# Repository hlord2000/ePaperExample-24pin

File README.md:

# A KiCAD 8 Schematic for Waveshare/Good Display 24-pin ePaper Displays

Based on the Waveshare ePaper shield. Includes links to parametric search for critical components.  

**Please refer to the datasheet for your specific driver IC to confirm component values and specifications.**

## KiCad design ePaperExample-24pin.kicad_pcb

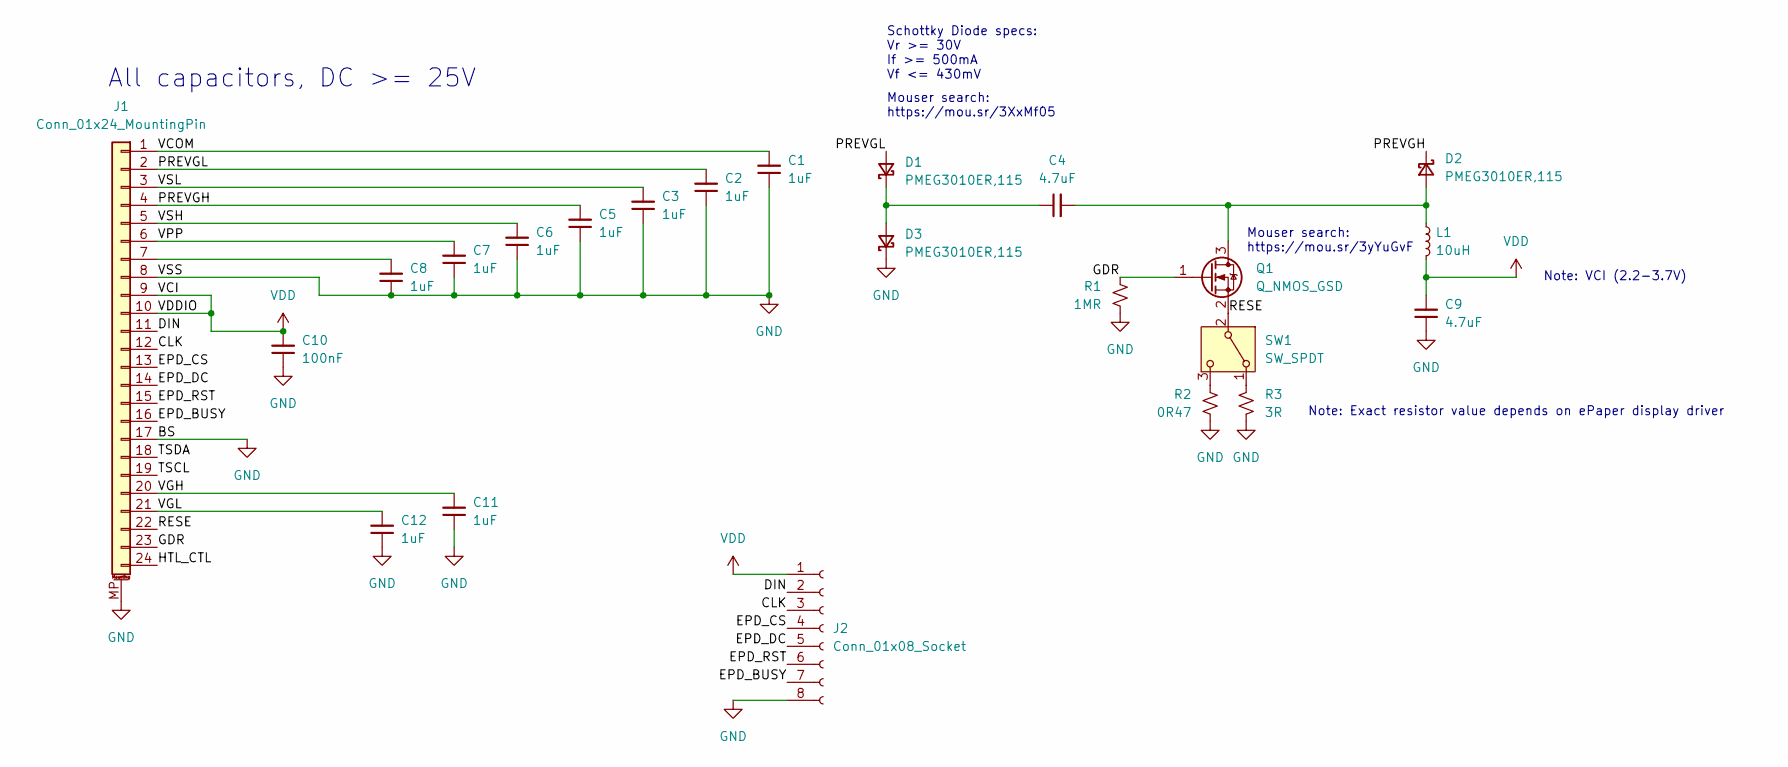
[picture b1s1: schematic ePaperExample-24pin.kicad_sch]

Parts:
C1, C2, C3, C5, C6, C7, C8, C11, C12: 1uF; C_0402_1005Metric; LCSC C52923
C4, C9: 4.7uF; C_0402_1005Metric; LCSC C2858031
C10: 100nF; C_0402_1005Metric; LCSC C307331
D1, D2, D3: PMEG3010ER,115; D_SOD-123; LCSC C456106
J1: Conn_01x24_MountingPin; TE_2-1734839-4_1x24-1MP_P0.5mm_Horizontal; LCSC C2911766
J2: Conn_01x08_Socket; PinHeader_1x08_P2.54mm_Vertical
L1: 10uH; L_0805_2012Metric; LCSC C2909263
Q1: Q_NMOS_GSD; SOT-23; LCSC C414015
R1: 1MR; R_0402_1005Metric; LCSC C26083
R2: 0R47; R_0603_1608Metric; LCSC C186564
R3: 3R; R_0603_1608Metric; LCSC C23157
SW1: SW_SPDT; SW_SPDT_PCM12; LCSC C109335

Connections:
/CLK: J1.12, J2.3
/DIN: J1.11, J2.2
/EPD_BUSY: J1.16, J2.7
/EPD_CS: J1.13, J2.4
/EPD_DC: J1.14, J2.5
/EPD_RST: J1.15, J2.6
/GDR: J1.23, Q1.1 (G), R1.1
/HTL_CTL: J1.24
/PREVGH: C5.2, D2.1 (K), J1.4
/PREVGL: C2.2, D1.2 (A), J1.2
/RESE: J1.22, Q1.2 (S), SW1.2 (B)
/TSCL: J1.19
/TSDA: J1.18
/VCOM: C1.2, J1.1
/VGH: C11.2, J1.20
/VGL: C12.2, J1.21
/VPP: C7.2, J1.6
/VSH: C6.2, J1.5
/VSL: C3.2, J1.3
GND: C1.1, C2.1, C3.1, C5.1, C6.1, C7.1, C8.1, C9.1, C10.1, C11.1, C12.1, D3.1 (K), J1.8, J1.17, J1.MP (MountPin), J2.8, R1.2, R2.2, R3.2
unnamed: C4.1, D1.1 (K), D3.2 (A)
unnamed: C4.2, D2.2 (A), L1.1, Q1.3 (D)
unnamed: C8.2, J1.7
unnamed: R3.1, SW1.1 (A)
unnamed: R2.1, SW1.3 (C)
VDD: C9.2, C10.2, J1.9, J1.10, J2.1, L1.2

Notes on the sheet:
Note: Exact resistor value depends on ePaper display driver
Note: VCI (2.2-3.7V)
Mouser search: https://mou.sr/3XxMf05
All capacitors, DC >= 25V
Mouser search: https://mou.sr/3yYuGvF
Schottky Diode specs: Vr >= 30V If >= 500mA Vf <= 430mV

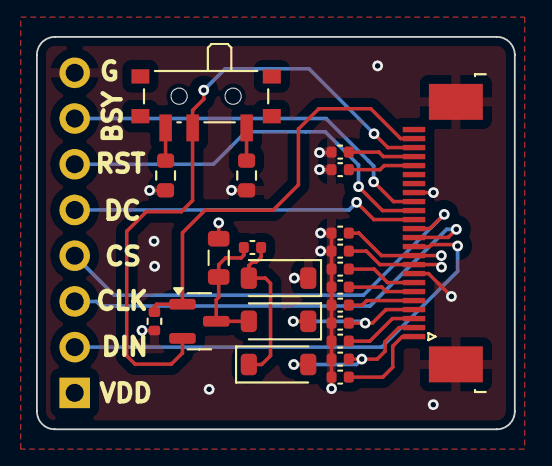
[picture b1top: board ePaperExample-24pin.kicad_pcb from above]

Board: 4 copper layers, 26.5 x 21.8 mm, 23 parts (1 on the bottom side), 23 nets.

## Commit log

2024-06-17 Initial commit.
2024-08-28 Updated to reflect tested board
2024-08-28 Updated image
2024-08-28 Added updated schematic, added PCB layout
2024-08-28 Updated README and images
